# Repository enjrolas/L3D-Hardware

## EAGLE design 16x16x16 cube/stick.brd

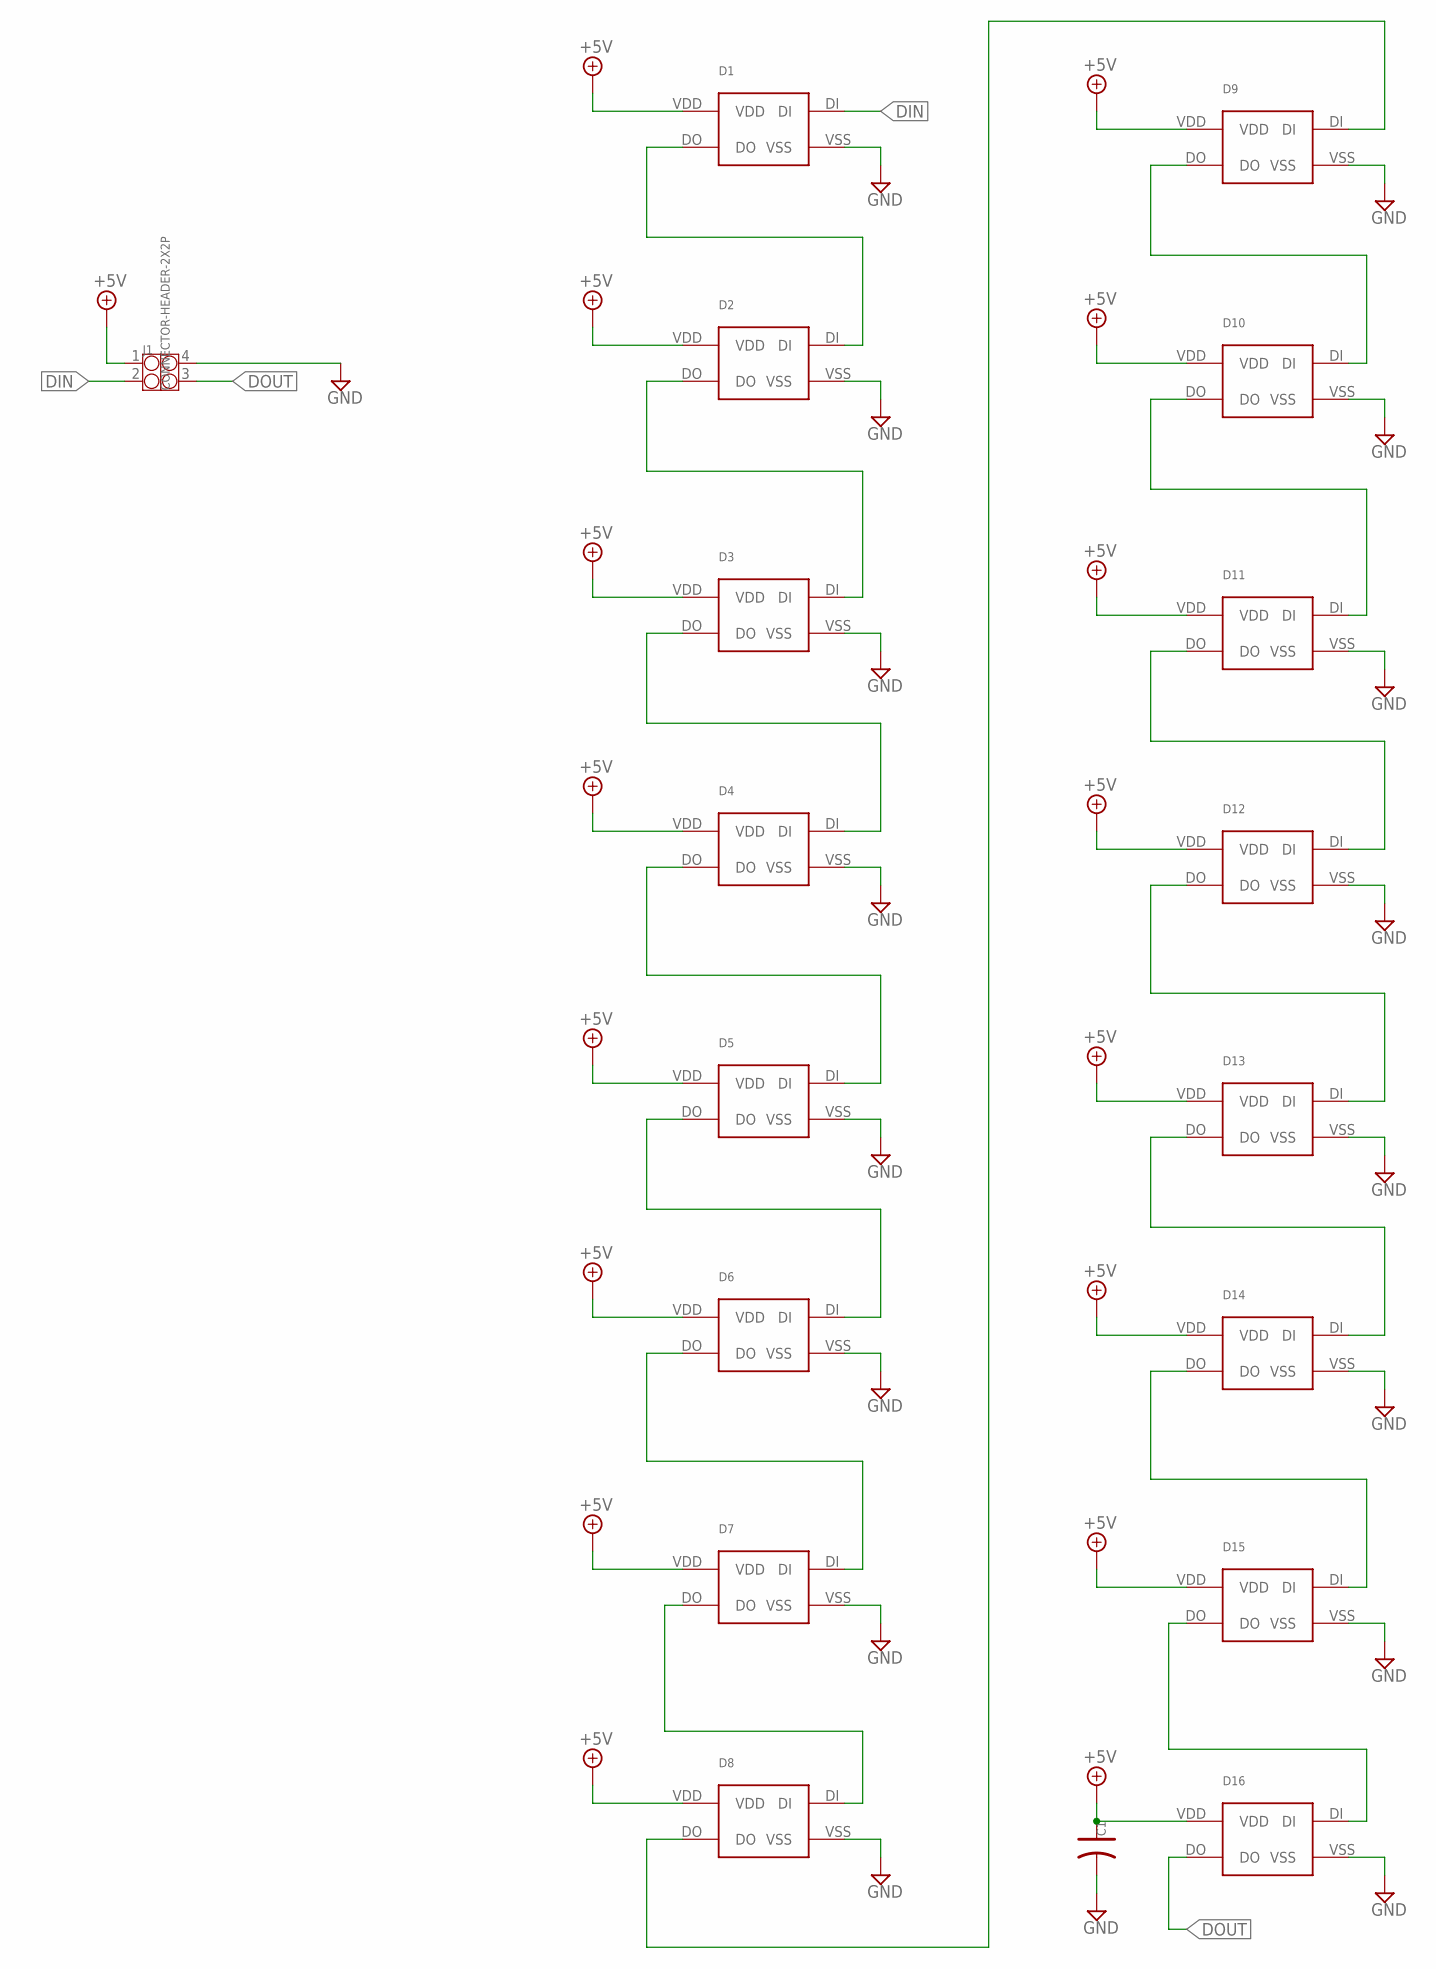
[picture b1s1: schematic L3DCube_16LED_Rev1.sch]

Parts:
C1: C-POLAR-A; AVX-A
D1, D2, D3, D4, D5, D6, D7, D8, D9, D10, D11, D12, D13, D14, D15, D16: WS2812B
J1: CONNECTOR-HEADER-2X2P; 2X2P-2.54

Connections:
+5V: C1.+ (1), D1.VDD, D2.VDD, D3.VDD, D4.VDD, D5.VDD, D6.VDD, D7.VDD, D8.VDD, D9.VDD, D10.VDD, D11.VDD, D12.VDD, D13.VDD, D14.VDD, D15.VDD, D16.VDD, J1.1
DIN: D1.DI, J1.2
DOUT: D16.DO, J1.3
GND: C1.- (2), D1.VSS, D2.VSS, D3.VSS, D4.VSS, D5.VSS, D6.VSS, D7.VSS, D8.VSS, D9.VSS, D10.VSS, D11.VSS, D12.VSS, D13.VSS, D14.VSS, D15.VSS, D16.VSS, J1.4
unnamed: D1.DO, D2.DI
unnamed: D2.DO, D3.DI
unnamed: D3.DO, D4.DI
unnamed: D4.DO, D5.DI
unnamed: D5.DO, D6.DI
unnamed: D6.DO, D7.DI
unnamed: D7.DO, D8.DI
unnamed: D9.DO, D10.DI
unnamed: D10.DO, D11.DI
unnamed: D11.DO, D12.DI
unnamed: D12.DO, D13.DI
unnamed: D13.DO, D14.DI
unnamed: D14.DO, D15.DI
unnamed: D15.DO, D16.DI
unnamed: D8.DO, D9.DI

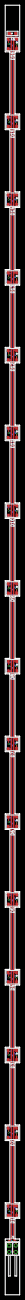
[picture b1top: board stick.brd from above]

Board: 2 copper layers, 5.6 x 497.5 mm, 18 parts (0 on the bottom side), 19 nets.

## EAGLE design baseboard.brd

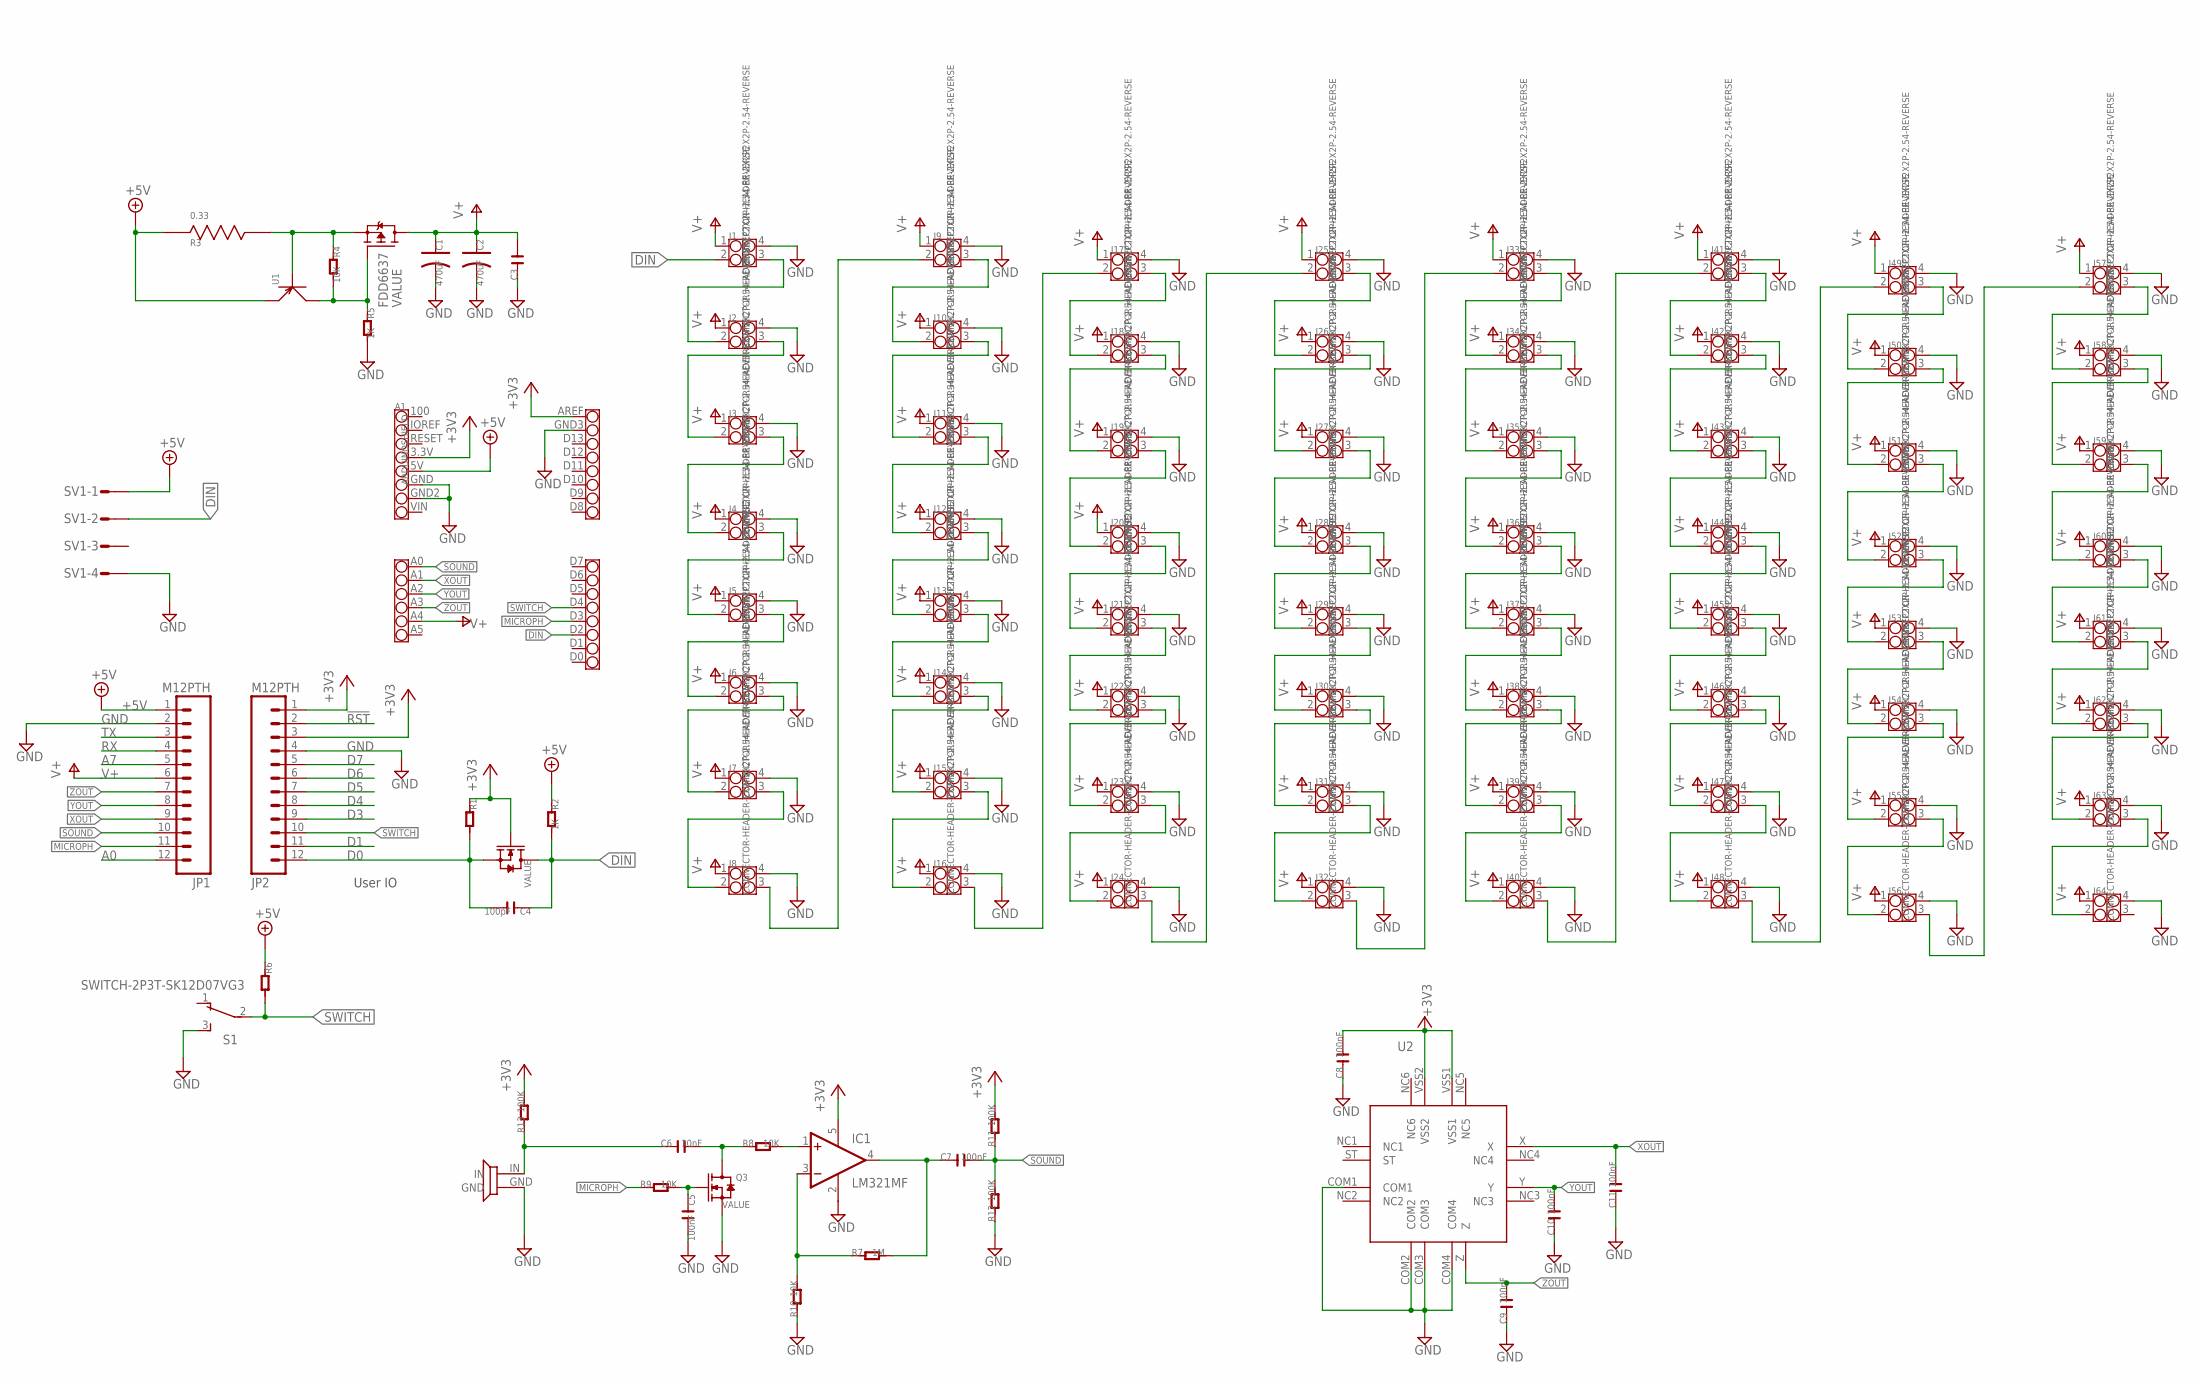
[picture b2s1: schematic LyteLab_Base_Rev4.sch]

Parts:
2N7002: MOSFET-N-044020001; SOT23
A1: ARDUINOSHIELD
C1, C2: 470uF; CAPACITOR-E5-8.5
C3: C-0603; C0603
C4: 100pF; C0603
C5, C7, C8, C9, C10, C11: 100nF; C0603
C6: 10nF; C0603
FDD6637: FDD4141TO252; TO252
IC1: LM321MF; SOT23-5
J1, J2, J3, J4, J5, J6, J7, J8, J9, J10, J11, J12, J13, J14, J15, J16, J17, J18, J19, J20, J21, J22, J23, J24, J25, J26, J27, J28, J29, J30, J31, J32, J33, J34, J35, J36, J37, J38, J39, J40, J41, J42, J43, J44, J45, J46, J47, J48, J49, J50, J51, J52, J53, J54, J55, J56, J57, J58, J59, J60, J61, J62, J63, J64: CONNECTOR-HEADER-2X2P2X2P-2.54-REVERSE; 2X2P-2.54-REVERSE
JP1, JP2: M12PTH; 1X12-SMALL-PADS
Q3: MOSFET-N-044020001; SOT23
R1, R6: R-0603; R0603
R2, R5: 1K; R0603
R3: 0.33; RESISTOR-3W-20MM
R4, R8, R9, R10: 10K; R0603
R7: 1M; R0603
R11, R12, R13: 100K; R0603
S1: SWITCH-2P3T-SK12D07VG3
SV1: S04P
U1: TRANSISTOR-PNP-041003001; SOT23
U2: ADXL335
U$1: MICROPHONE

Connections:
!RST: JP2.2
+3V3: 2N7002.1 (G), A1.3.3V, A1.AREF, C8.2, IC1.5 (V+), JP2.1, JP2.3, R1.1, R11.2, R13.2, U2.VSS1, U2.VSS2
+5V: A1.5V, JP1.1, R2.1, R3.1, R6.1, SV1.1, U1.2 (E)
A0: JP1.12
A7: JP1.5
D0: 2N7002.2 (S), C4.2, JP2.12, R1.2
D1: JP2.11
D3: JP2.9
D4: JP2.8
D5: JP2.7
D6: JP2.6
D7: JP2.5
DIN: 2N7002.3 (D), A1.D2, C4.1, J1.2, R2.2, SV1.2
GND: A1.GND, A1.GND2, A1.GND3, C1.- (2), C2.- (2), C3.1, C5.2, C8.1, C9.1, C10.1, C11.1, IC1.2 (V-), J1.4, J2.4, J3.4, J4.4, J5.4, J6.4, J7.4, J8.4, J9.4, J10.4, J11.4, J12.4, J13.4, J14.4, J15.4, J16.4, J17.4, J18.4, J19.4, J20.4, J21.4, J22.4, J23.4, J24.4, J25.4, J26.4, J27.4, J28.4, J29.4, J30.4, J31.4, J32.4, J33.4, J34.4, J35.4, J36.4, J37.4, J38.4, J39.4, J40.4, J41.4, J42.4, J43.4, J44.4, J45.4, J46.4, J47.4, J48.4, J49.4, J50.4, J51.4, J52.4, J53.4, J54.4, J55.4, J56.4, J57.4, J58.4, J59.4, J60.4, J61.4, J62.4, J63.4, J64.4, JP1.2, JP2.4, Q3.2 (S), R5.2, R10.1, R12.1, S1.3 (S), SV1.4, U2.COM1, U2.COM2, U2.COM3, U2.COM4, U$1.GND
MICROPH: A1.D3, JP1.11, R9.1
unnamed: J1.3, J2.2
unnamed: J2.3, J3.2
unnamed: J3.3, J4.2
unnamed: J5.3, J6.2
unnamed: J6.3, J7.2
unnamed: J7.3, J8.2
unnamed: J4.3, J5.2
unnamed: J9.3, J10.2
unnamed: J10.3, J11.2
unnamed: J11.3, J12.2
unnamed: J13.3, J14.2
unnamed: J14.3, J15.2
unnamed: J15.3, J16.2
unnamed: J12.3, J13.2
unnamed: J17.3, J18.2
unnamed: J18.3, J19.2
unnamed: J19.3, J20.2
unnamed: J21.3, J22.2
unnamed: J22.3, J23.2
unnamed: J23.3, J24.2
unnamed: J20.3, J21.2
unnamed: J25.3, J26.2
unnamed: J26.3, J27.2
unnamed: J27.3, J28.2
unnamed: J29.3, J30.2
unnamed: J30.3, J31.2
unnamed: J31.3, J32.2
unnamed: J28.3, J29.2
unnamed: J8.3, J9.2
unnamed: J16.3, J17.2
unnamed: J24.3, J25.2
unnamed: C7.1, IC1.4 (OUT), R7.2
unnamed: J33.3, J34.2
unnamed: J34.3, J35.2
unnamed: J35.3, J36.2
unnamed: J37.3, J38.2
unnamed: J38.3, J39.2
unnamed: J39.3, J40.2
unnamed: J36.3, J37.2
unnamed: J41.3, J42.2
unnamed: J42.3, J43.2
unnamed: J43.3, J44.2
unnamed: J45.3, J46.2
unnamed: J46.3, J47.2
unnamed: J47.3, J48.2
unnamed: J44.3, J45.2
unnamed: J49.3, J50.2
unnamed: J50.3, J51.2
unnamed: J51.3, J52.2
unnamed: J53.3, J54.2
unnamed: J54.3, J55.2
unnamed: J55.3, J56.2
unnamed: J52.3, J53.2
unnamed: J57.3, J58.2
unnamed: J58.3, J59.2
unnamed: J59.3, J60.2
unnamed: J61.3, J62.2
unnamed: J62.3, J63.2
unnamed: J63.3, J64.2
unnamed: J60.3, J61.2
unnamed: J40.3, J41.2
unnamed: J48.3, J49.2
unnamed: J56.3, J57.2
unnamed: J32.3, J33.2
unnamed: FDD6637.2 (S), R3.2, R4.1, U1.1 (B)
unnamed: IC1.3 (-IN), R7.1, R10.2
unnamed: FDD6637.1 (G), R4.2, R5.1, U1.3 (C)
unnamed: C5.1, Q3.1 (G), R9.2
unnamed: IC1.1 (+IN), R8.2
unnamed: C6.2, Q3.3 (D), R8.1
unnamed: C6.1, R13.1, U$1.IN
RX: JP1.4
SOUND: A1.A0, C7.2, JP1.10, R11.1, R12.2
SWITCH: A1.D4, JP2.10, R6.2, S1.2
TX: JP1.3
V+: A1.A4, C1.+ (1), C2.+ (1), C3.2, FDD6637.3 (D), J1.1, J2.1, J3.1, J4.1, J5.1, J6.1, J7.1, J8.1, J9.1, J10.1, J11.1, J12.1, J13.1, J14.1, J15.1, J16.1, J17.1, J18.1, J19.1, J20.1, J21.1, J22.1, J23.1, J24.1, J25.1, J26.1, J27.1, J28.1, J29.1, J30.1, J31.1, J32.1, J33.1, J34.1, J35.1, J36.1, J37.1, J38.1, J39.1, J40.1, J41.1, J42.1, J43.1, J44.1, J45.1, J46.1, J47.1, J48.1, J49.1, J50.1, J51.1, J52.1, J53.1, J54.1, J55.1, J56.1, J57.1, J58.1, J59.1, J60.1, J61.1, J62.1, J63.1, J64.1, JP1.6
XOUT: A1.A1, C11.2, JP1.9, U2.X
YOUT: A1.A2, C10.2, JP1.8, U2.Y
ZOUT: A1.A3, C9.2, JP1.7, U2.Z

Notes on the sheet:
User IO

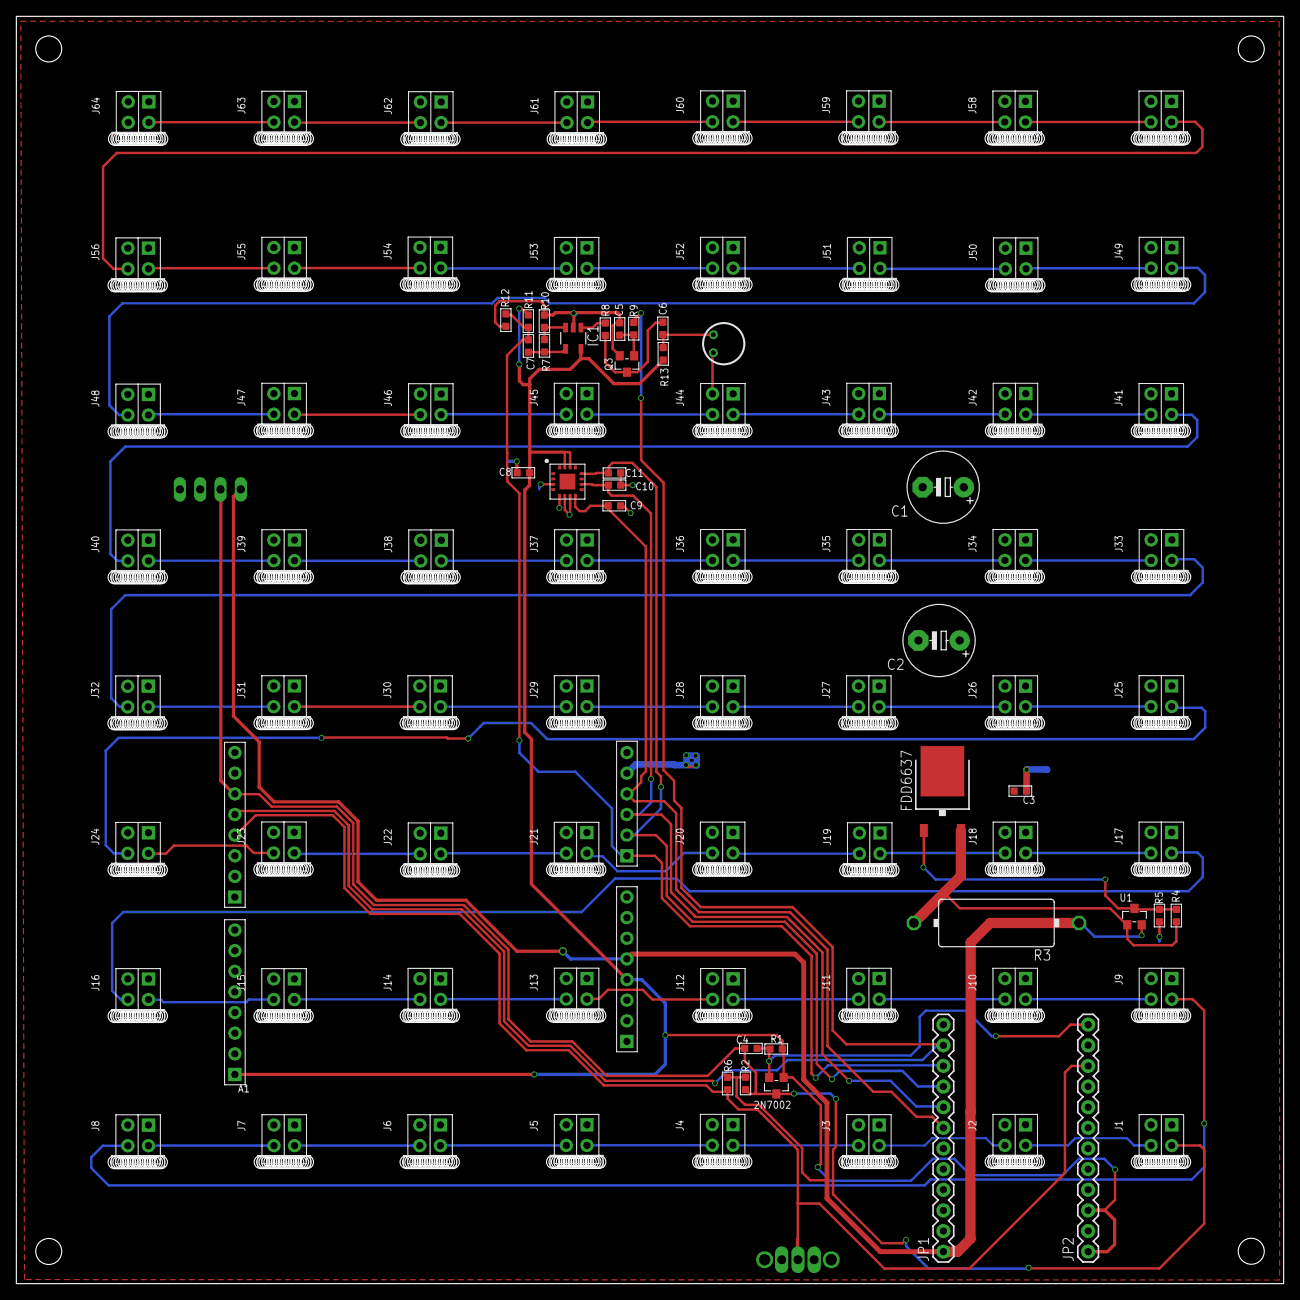
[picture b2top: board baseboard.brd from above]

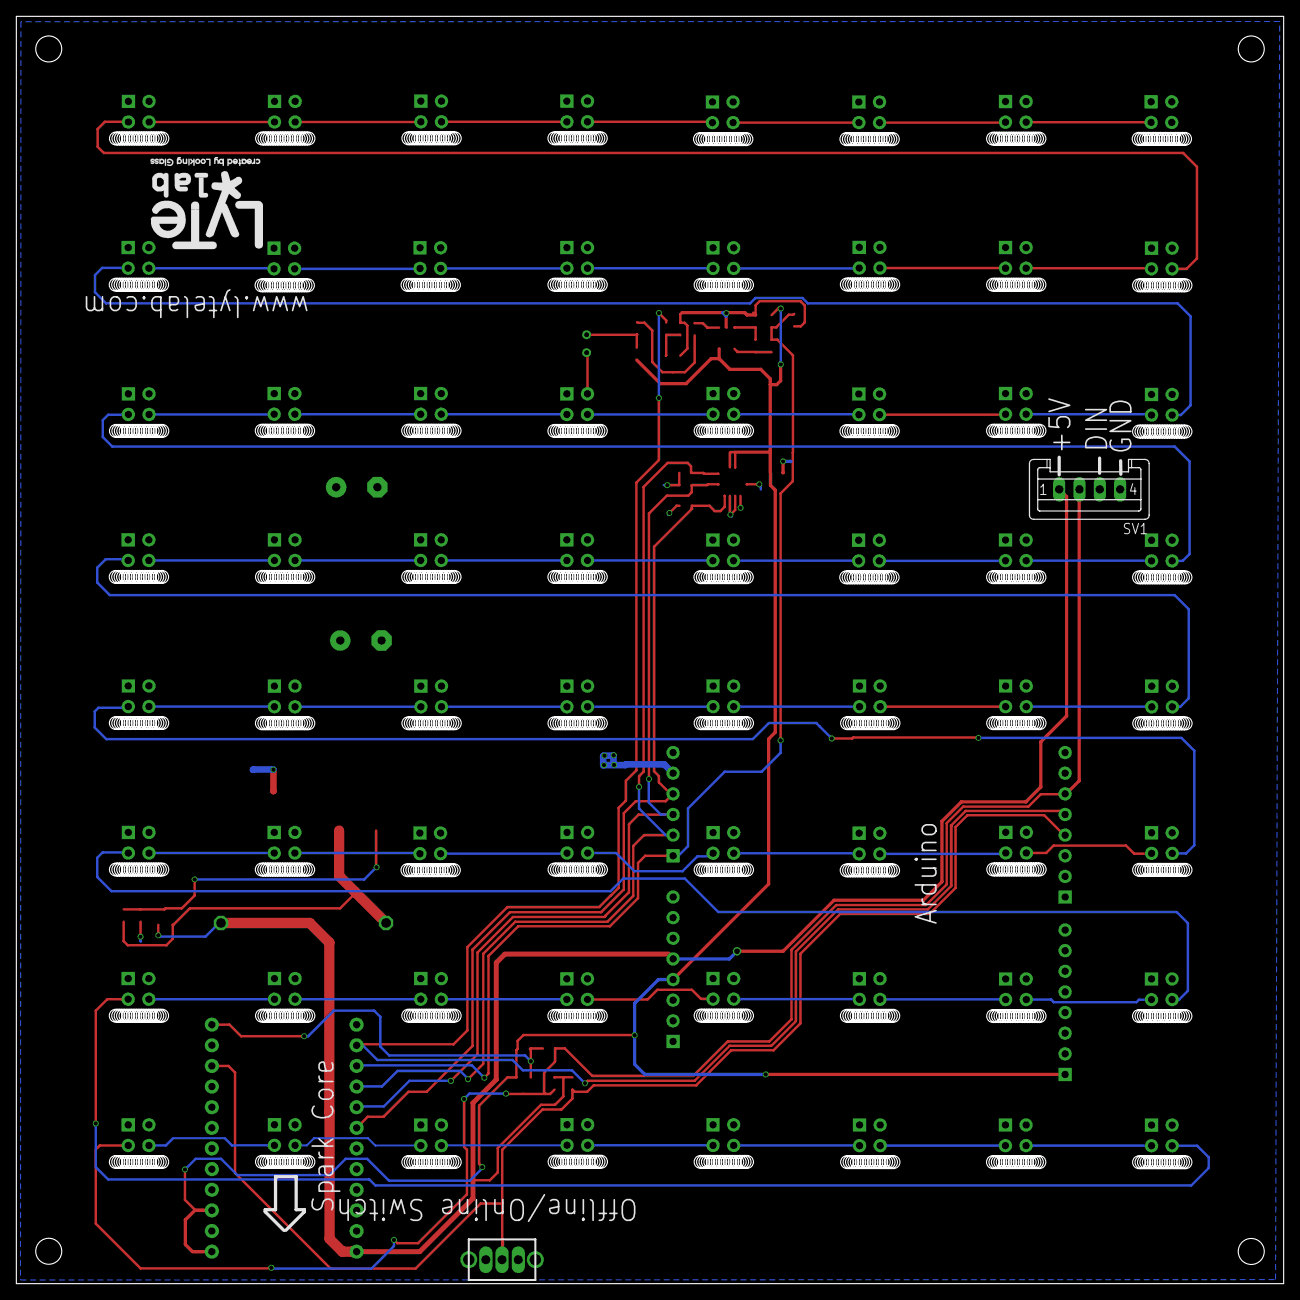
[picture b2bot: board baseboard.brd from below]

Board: 2 copper layers, 156.0 x 156.0 mm, 100 parts (2 on the bottom side), 83 nets.
